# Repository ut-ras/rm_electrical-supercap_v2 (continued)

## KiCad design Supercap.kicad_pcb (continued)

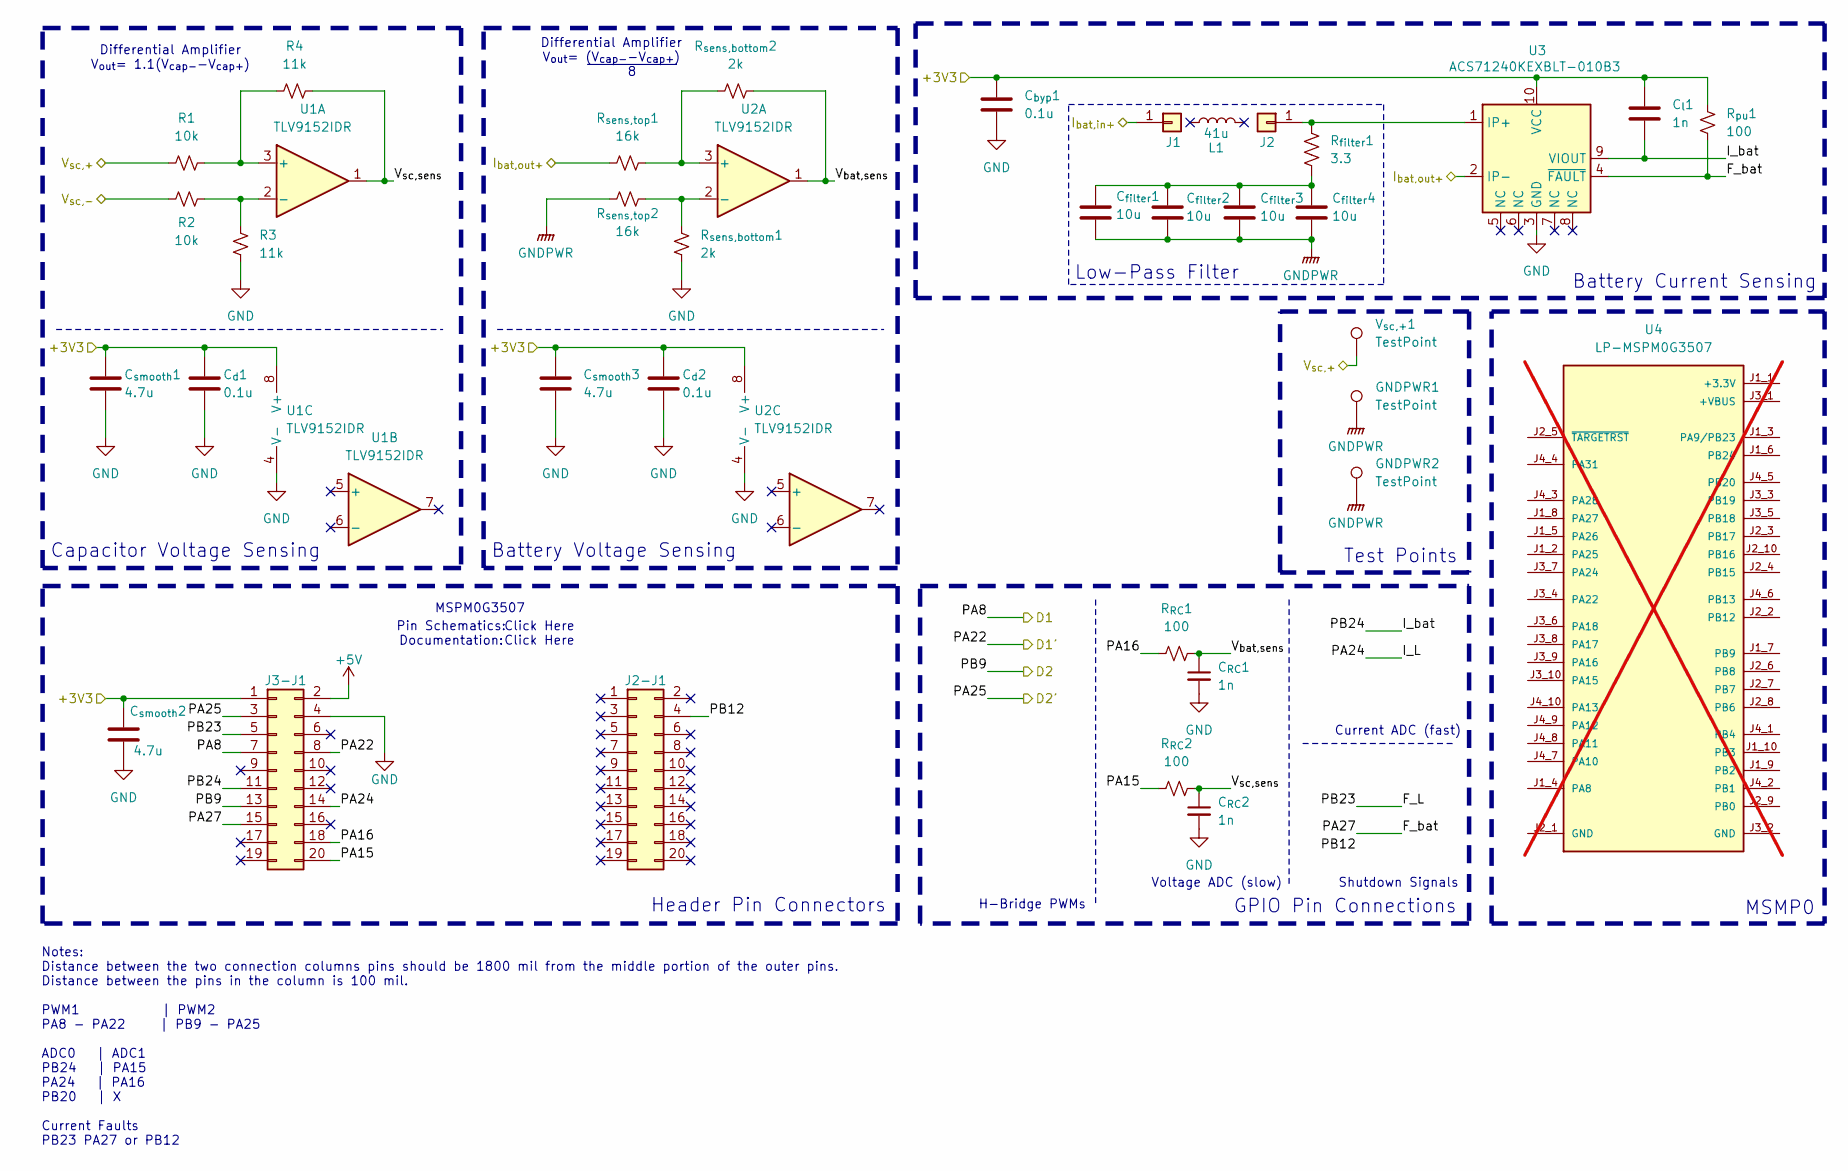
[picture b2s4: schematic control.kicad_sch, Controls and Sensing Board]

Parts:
C_{RC}1, C_{RC}2: 1n; C_0603_1608Metric_Pad1.08x0.95mm_HandSolder; Manufacturer_Part_Number CC0603JRX7R7BB102; Mouser Part Number 603-CC0603JR7R7BB102
C_{byp}1: 0.1u; C_0603_1608Metric_Pad1.08x0.95mm_HandSolder; Manufacturer_Part_Number MCAST168SB5104KTNA01; Mouser Part Number 963-MCAST168SB5104KT
C_{d}1, C_{d}2: 0.1u; C_0603_1608Metric_Pad1.08x0.95mm_HandSolder; Manufacturer_Part_Number KGM15BR71H104JM; Mouser Part Number 581-KGM15BR71H104JM
C_{filter}1, C_{filter}2, C_{filter}3, C_{filter}4: 10u; C_0603_1608Metric_Pad1.08x0.95mm_HandSolder; Mouser# 81-GRM188R6YA106MA3D
C_{l}1: 1n; C_0603_1608Metric_Pad1.08x0.95mm_HandSolder; Manufacturer_Part_Number CC0603JRX7R7BB102; Mouser Part Number 603-CC0603JR7R7BB102
C_{smooth}1, C_{smooth}2, C_{smooth}3: 4.7u; C_0603_1608Metric_Pad1.08x0.95mm_HandSolder; Manufacturer_Part_Number CL10A475KO8NNNC; Mouser Part Number 187-CL10A475KO8NNNC
GNDPWR1, GNDPWR2: TestPoint; TestPoint_Bridge_Pitch2.0mm_Drill0.7mm
J1, J2: Conn_01x01; Inductor_wire_conn
J2-J1, J3-J1: Conn_01x10; PinSocket_2x10_P2.54mm_Vertical; Manufacturer_Part_Number 2044-2X10G00SA; Digi-Key Part Number 2553-2044-2X10G00SA-ND
L1: 41u
R1, R2: 10k; R_0603_1608Metric_Pad0.98x0.95mm_HandSolder; Manufacturer_Part_Number RN73R1JTTD1002B50; Mouser Part Number 660-RN73R1JTD1002B50
R3, R4: 11k; R_0603_1608Metric_Pad0.98x0.95mm_HandSolder; Manufacturer_Part_Number RN73R1JTTD1102B25; Mouser Part Number 660-RN73R1JTD1102B25
R_{RC}1, R_{RC}2: 100; R_0603_1608Metric_Pad0.98x0.95mm_HandSolder; Manufacturer_Part_Number CRGCQ0603F100R; Mouser Part Number 279-CRGCQ0603F100R
R_{filter}1: 3.3; R_0603_1608Metric_Pad0.98x0.95mm_HandSolder; Manufacturer_Part_Number ERJ-H3QD3R30V; Mouser Part Number 667-ERJ-H3QD3R30V
R_{pu}1: 100; R_0603_1608Metric_Pad0.98x0.95mm_HandSolder; Manufacturer_Part_Number CRGCQ0603F100R; Mouser Part Number 279-CRGCQ0603F100R
R_{sens,bottom}1, R_{sens,bottom}2: 2k; R_0603_1608Metric_Pad0.98x0.95mm_HandSolder; Manufacturer_Part_Number AT0603DRD072KL; Mouser Part Number 603-AT0603DRD072KL
R_{sens,top}1, R_{sens,top}2: 16k; R_0603_1608Metric_Pad0.98x0.95mm_HandSolder; Manufacturer_Part_Number RT0603DRD0716KL; Mouser Part Number 603-RT0603DRD0716KL
U1, U2: TLV9152IDR; SOIC-8_3.9x4.9mm_P1.27mm; Manufacturer_Part_Number TLV9152IDR; Mouser Part Number 595-TLV9152IDR
U3: ACS71240KEXBLT-010B3; Allegro_QFN-12-10-1EP_3x3mm_P0.5mm; Manufacturer_Part_Number ACS71240KEXBLT-010B3; Mouser Part Number 250-71240KEXBLT010B3
U4: LP-MSPM0G3507; ti_LP_MSPM0G3507; not fitted
V_{sc,+}1: TestPoint; TestPoint_Bridge_Pitch2.0mm_Drill0.7mm

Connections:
+5V: J3-J1.2
/Control/+3V3: C_{byp}1.1, C_{d}1.1, C_{d}2.1, C_{l}1.1, C_{smooth}1.1, C_{smooth}2.1, C_{smooth}3.1, J3-J1.1, R_{pu}1.2, U1.8 (V+), U2.8 (V+), U3.10 (VCC); also elsewhere on the board
/Control/F_L: J3-J1.5
/Control/F_bat: J3-J1.15, R_{pu}1.1, U3.4 (~FAULT)
/Control/I_L: J3-J1.14
/Control/I_bat: C_{l}1.2, J3-J1.11, U3.9 (VIOUT)
/Control/I_{bat,in+}: J1.1; also elsewhere on the board
/Control/I_{bat,out+}: R_{sens,top}1.1, U3.2 (IP-); also elsewhere on the board
/Control/PA8: J3-J1.7; also elsewhere on the board
/Control/PA15: J3-J1.20, R_{RC}2.2
/Control/PA16: J3-J1.18, R_{RC}1.2
/Control/PA22: J3-J1.8; also elsewhere on the board
/Control/PA25: J3-J1.3; also elsewhere on the board
/Control/PB9: J3-J1.13; also elsewhere on the board
/Control/PB12: J2-J1.4
/Control/V_{bat,sens}: C_{RC}1.1, R_{RC}1.1, R_{sens,bottom}2.2, U2.1
/Control/V_{sc,+}: R1.1, V_{sc,+}1.1; also elsewhere on the board
/Control/V_{sc,sens}: C_{RC}2.1, R4.2, R_{RC}2.1, U1.1
/Voltage Converter/V_{sw,2}: R2.1; also elsewhere on the board
GND: C_{RC}1.2, C_{RC}2.2, C_{byp}1.2, C_{d}1.2, C_{d}2.2, C_{smooth}1.2, C_{smooth}2.2, C_{smooth}3.2, J3-J1.4, R3.2, R_{sens,bottom}1.1, U1.4 (V-), U2.4 (V-), U3.3 (GND); also elsewhere on the board
GNDPWR: C_{filter}1.2, C_{filter}2.2, C_{filter}3.2, C_{filter}4.2, GNDPWR1.1, GNDPWR2.1, R_{sens,top}2.1; also elsewhere on the board
unnamed: C_{filter}1.1, C_{filter}2.1, C_{filter}3.1, C_{filter}4.1, R_{filter}1.2
unnamed: J2.1, R_{filter}1.1, U3.1 (IP+)
unnamed: R1.2, R4.1, U1.3 (+)
unnamed: R2.2, R3.1, U1.2 (-)
unnamed: R_{sens,bottom}2.1, R_{sens,top}1.2, U2.3 (+)
unnamed: R_{sens,bottom}1.2, R_{sens,top}2.2, U2.2 (-)

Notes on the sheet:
Shutdown Signals
Pin Schematics: Documentation:
MSMP0
MSPM0G3507
Battery Current Sensing
Current ADC (fast)
Low-Pass Filter
Voltage ADC (slow)
Header Pin Connectors
Click Here
Differential Amplifier V_{out}= (V_{cap-}-V_{cap+}) ~{ 8 }
Test Points
GPIO Pin Connections
H-Bridge PWMs
Capacitor Voltage Sensing
Battery Voltage Sensing
Differential Amplifier V_{out}= 1.1(V_{cap-}-V_{cap+})
Notes: Distance between the two connection columns pins should be 1800 mil from the middle portion of the outer pins. Distance between the pins in the column is 100 mil. PWM1 | PWM2 PA8 - PA22 | PB9 - PA25 ADC0 | ADC1 PB24 | PA15 PA24 | PA16 PB20 | X Current Faults PB23 PA27 or PB12

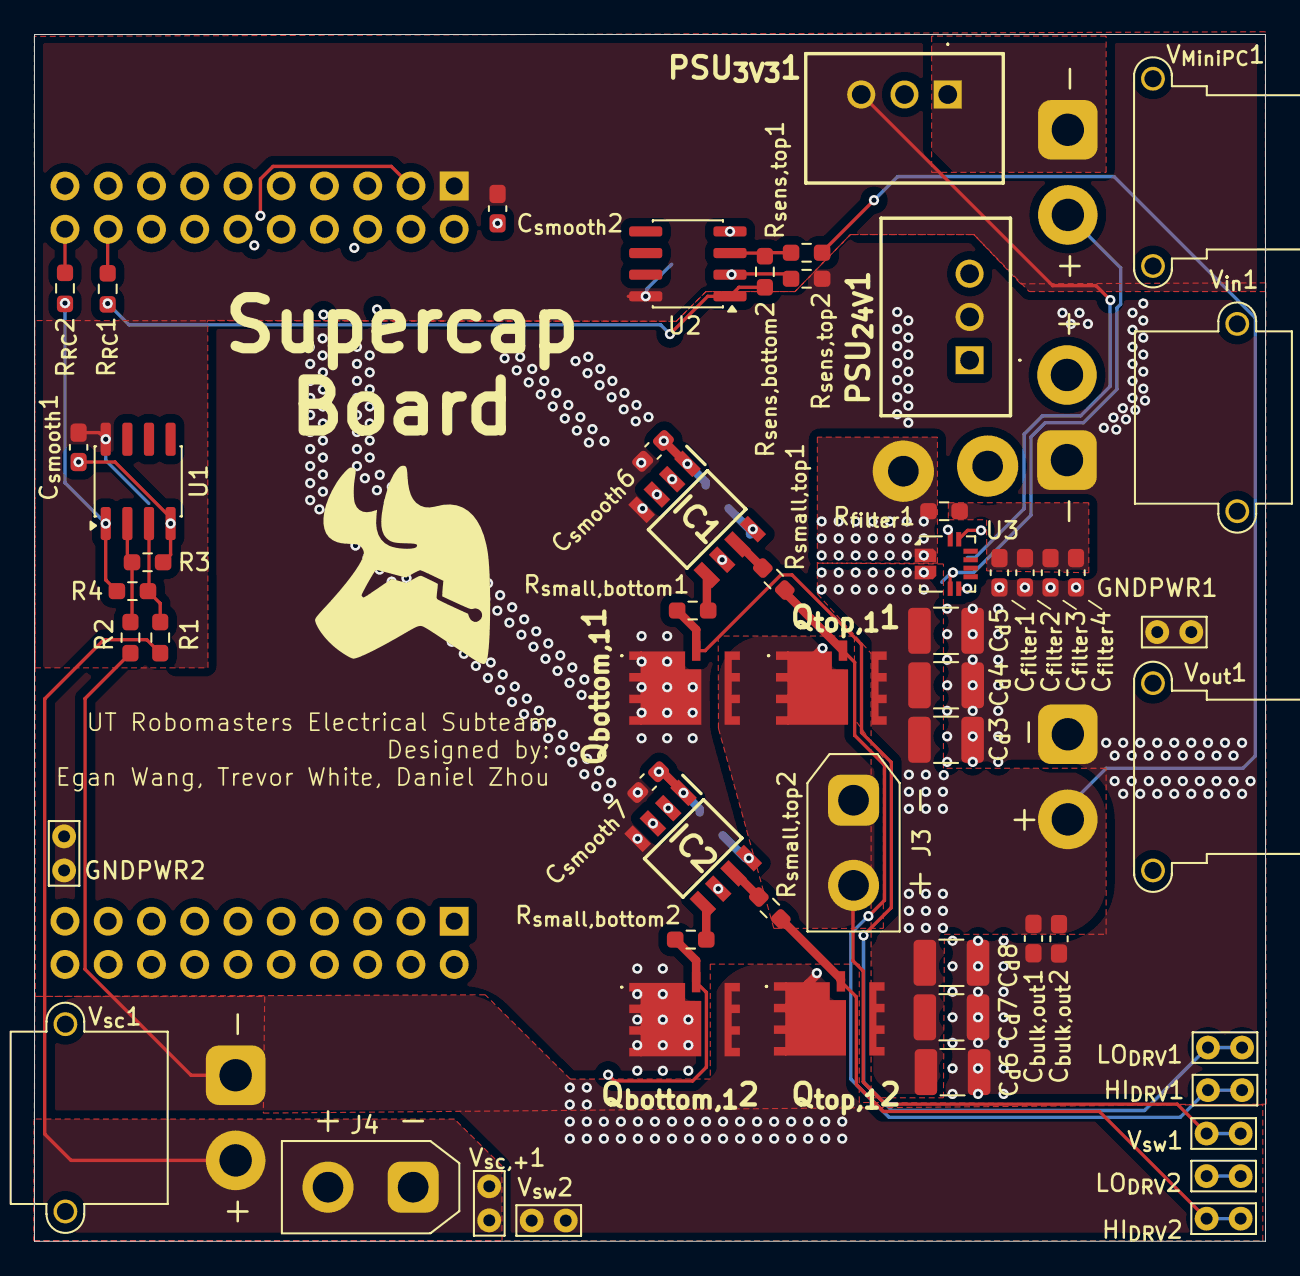
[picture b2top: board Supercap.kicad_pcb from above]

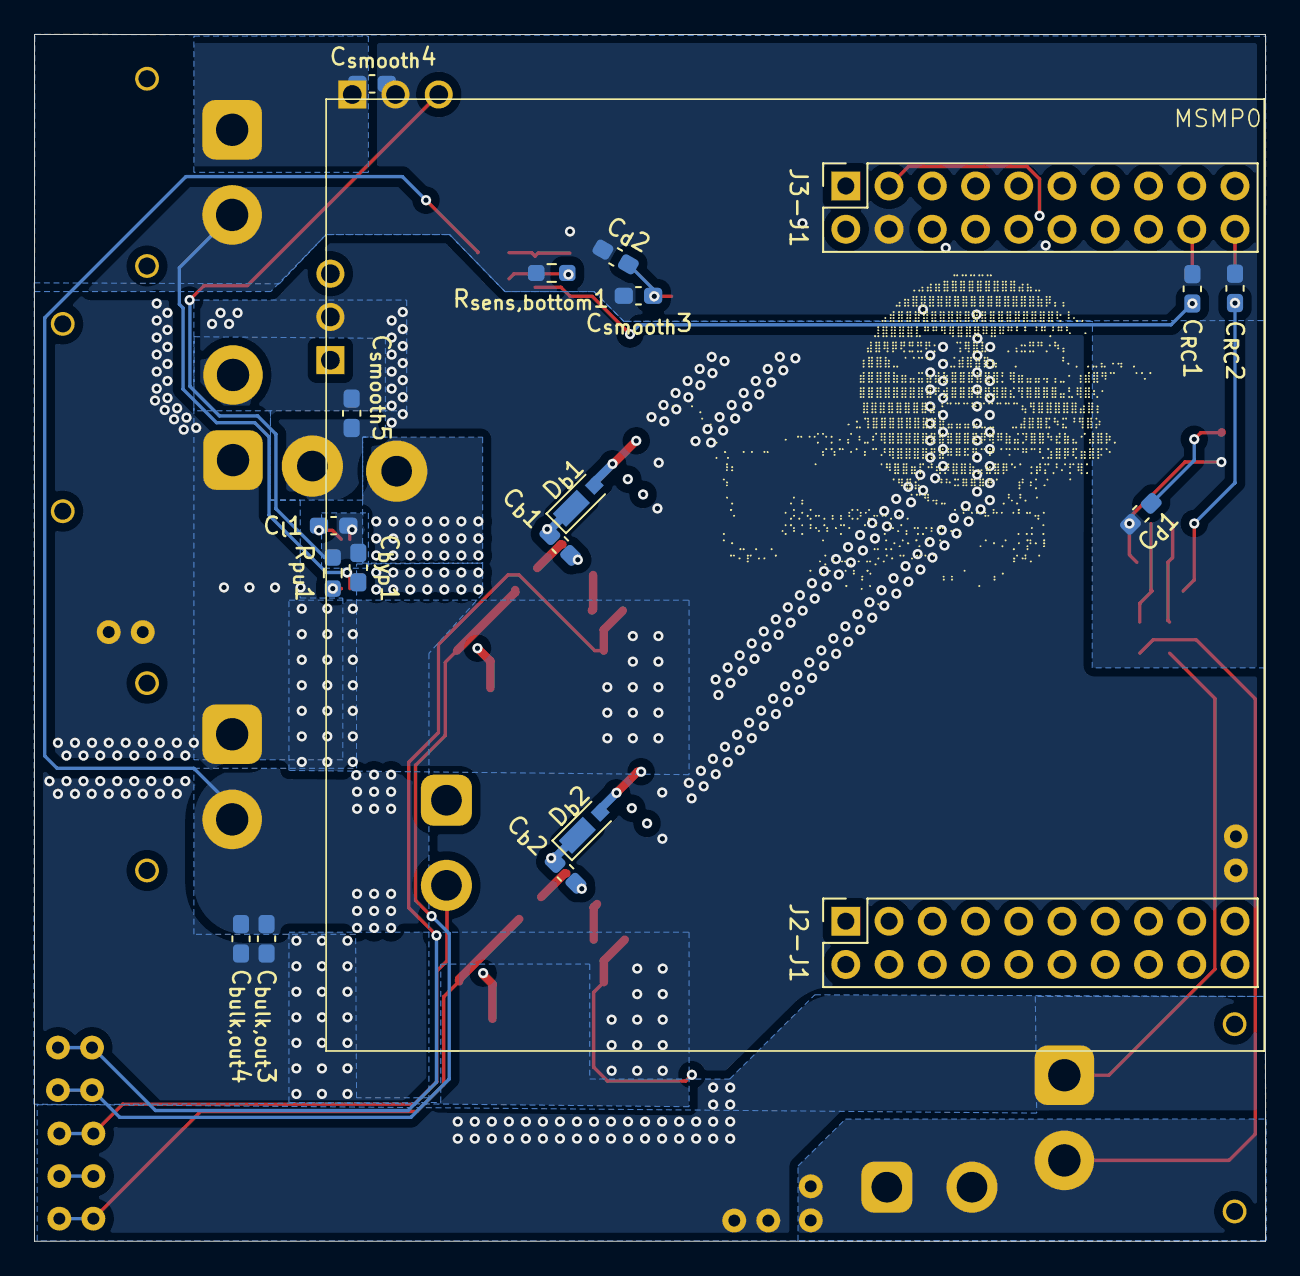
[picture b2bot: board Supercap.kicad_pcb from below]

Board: 4 copper layers, 72.3 x 70.9 mm, 77 parts (20 on the bottom side), 36 nets.

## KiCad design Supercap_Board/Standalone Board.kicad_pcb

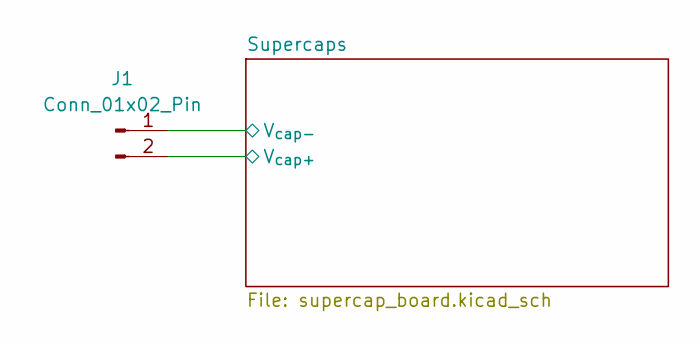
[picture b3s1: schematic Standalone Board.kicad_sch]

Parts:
J1: Conn_01x02_Pin; AMASS_XT30UPB-F_1x02_P5.0mm_Vertical

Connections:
/Supercaps/V_{cap+}: J1.2; also elsewhere on the board
/Supercaps/V_{cap-}: J1.1; also elsewhere on the board

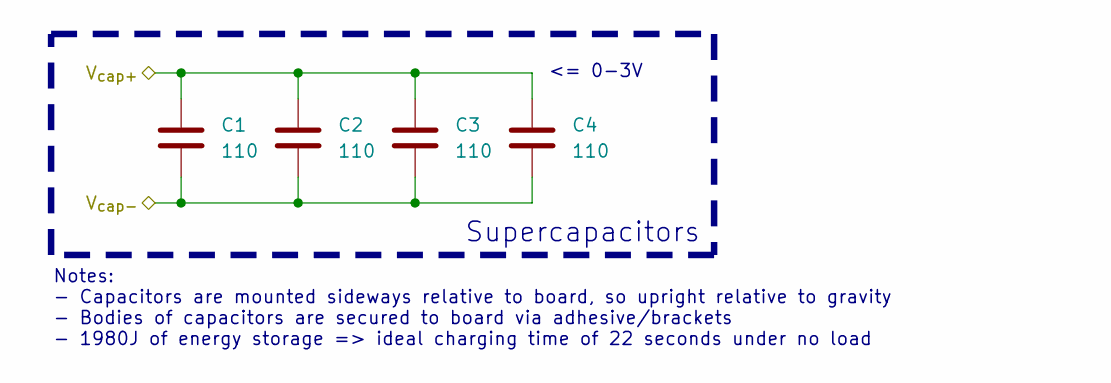
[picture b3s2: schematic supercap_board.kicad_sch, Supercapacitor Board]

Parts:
C1, C2, C3, C4: 110; C_Radial_D18.0mm_H35.5mm_P7.50mm; Voltage Rating 3V; Mouser Part Number 598-DSF117Q3R0

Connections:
/Supercaps/V_{cap+}: C1.1, C2.1, C3.1, C4.1; also elsewhere on the board
/Supercaps/V_{cap-}: C1.2, C2.2, C3.2, C4.2; also elsewhere on the board

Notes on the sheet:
Notes: - Capacitors are mounted sideways relative to board, so upright relative to gravity - Bodies of capacitors are secured to board via adhesive/brackets - 1980J of energy storage => ideal charging time of 22 seconds under no load
Supercapacitors
<= 0-3V

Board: 2 copper layers, 5 parts (0 on the bottom side), 2 nets, no tracks yet.

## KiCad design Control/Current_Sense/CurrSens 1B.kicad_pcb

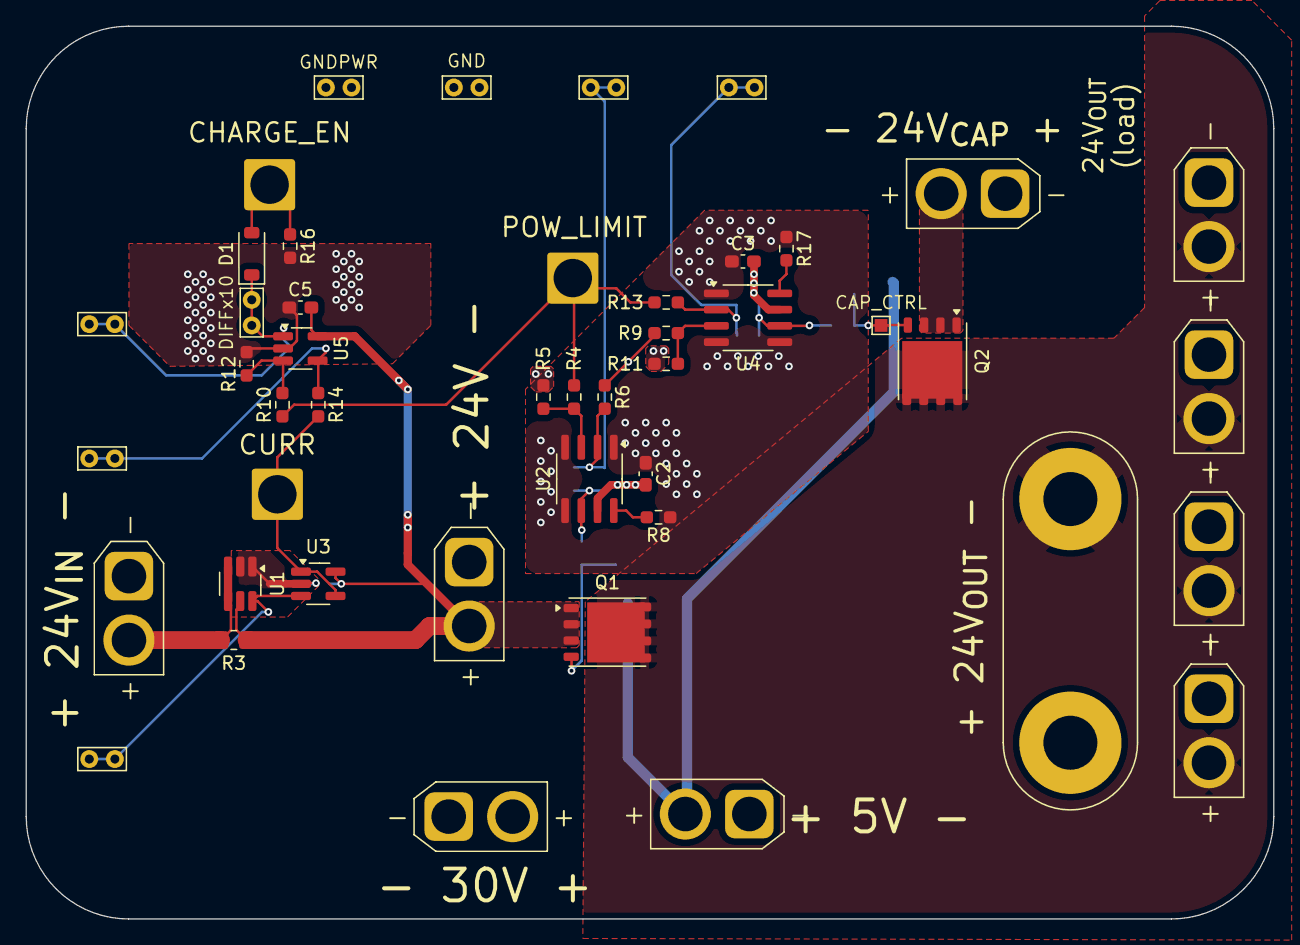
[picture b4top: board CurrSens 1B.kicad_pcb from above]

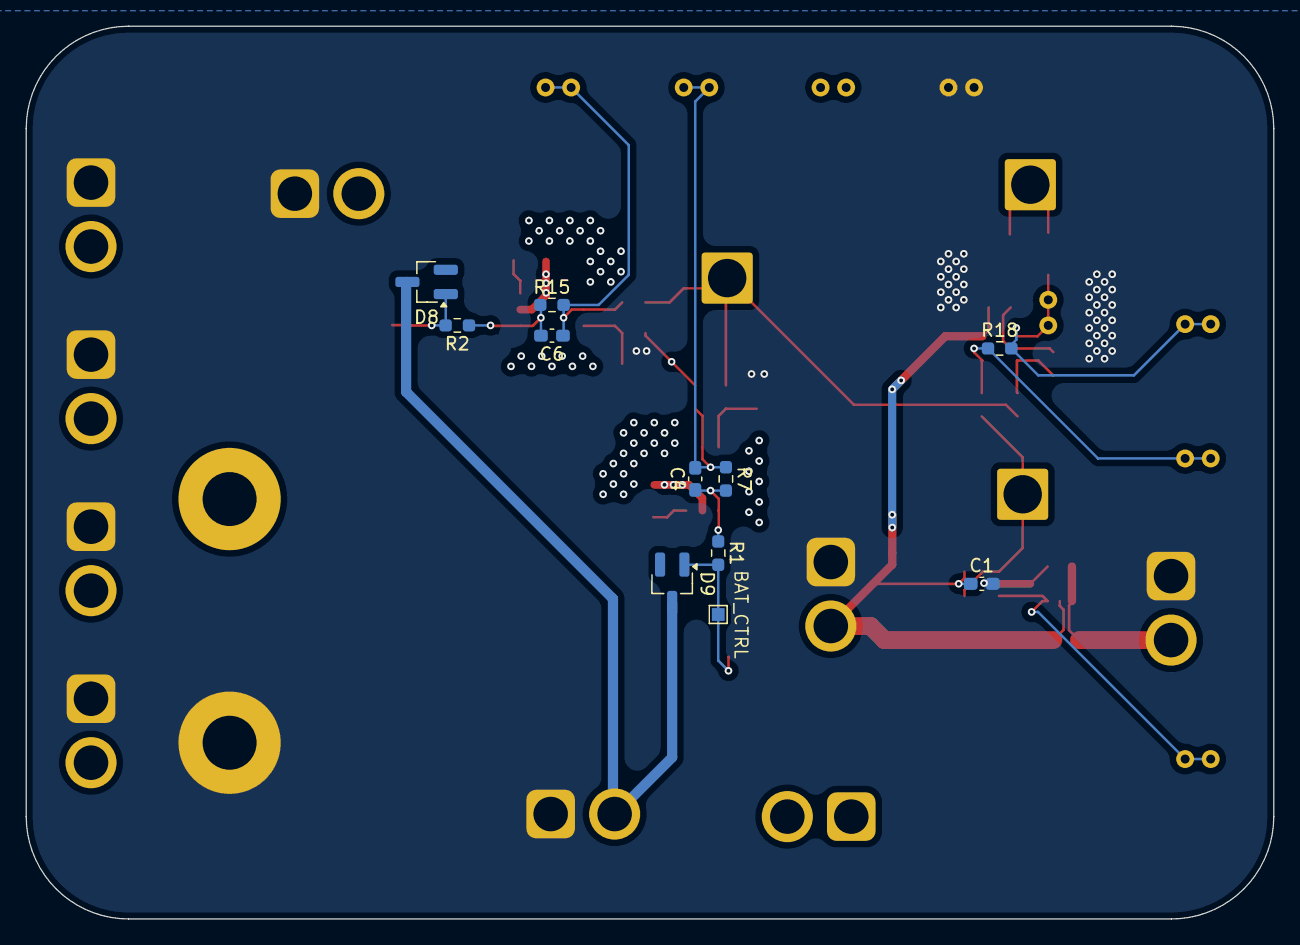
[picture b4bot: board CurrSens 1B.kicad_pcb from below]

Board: 4 copper layers, 97.5 x 69.8 mm, 57 parts (11 on the bottom side), 25 nets.

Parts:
C1, C2, C3, C5: 0.1u; C_0603_1608Metric_Pad1.08x0.95mm_HandSolder
C4, C6: 1000p; C_0603_1608Metric_Pad1.08x0.95mm_HandSolder
D1: MMSZ4678T1G; D_SOD-123
D8, D9: BAT54; SOT-23_Handsoldering
J1, J2, J10: Conn_01x01_Pin; SolderWire-2.5sqmm_1x01_D2.4mm_OD3.6mm
J3, J6, J7, J9, J11, J12, J13, J14, J15: XT30_F; AMASS_XT30U-F_1x02_P5.0mm_Vertical
J16: Banana; RM_Banana_Jack_2Pin
Q1, Q2: BSC059N04LS6; Infineon_PG-TDSON-8_6.15x5.15mm
R1, R2: 0; R_0603_1608Metric_Pad0.98x0.95mm_HandSolder
R3: 0.02; R_0805_2012Metric_Pad1.20x1.40mm_HandSolder
R4, R6, R9, R13: 1k; R_0603_1608Metric_Pad0.98x0.95mm_HandSolder
R5, R7, R11, R12, R15, R18: 1Meg; R_0603_1608Metric_Pad0.98x0.95mm_HandSolder
R8, R17: 47k; R_0603_1608Metric_Pad0.98x0.95mm_HandSolder
R10, R14: 100k; R_0603_1608Metric_Pad0.98x0.95mm_HandSolder
R16: 15k; R_0603_1608Metric_Pad0.98x0.95mm_HandSolder
TP1, TP2, TP3: V_{DIFF10}; TestPoint_Bridge_Pitch2.0mm_Drill0.7mm
TP4, TP5: V_{DIFF10}; TestPoint_Pad_1.0x1.0mm
TP6: CE_OUT; TestPoint_Bridge_Pitch2.0mm_Drill0.7mm
TP7: CE_IN_NEG; TestPoint_Bridge_Pitch2.0mm_Drill0.7mm
TP8: I_OUT; TestPoint_Bridge_Pitch2.0mm_Drill0.7mm
TP9: CAP_IN_NEG; TestPoint_Bridge_Pitch2.0mm_Drill0.7mm
TP10: BAT_IN_NEG; TestPoint_Bridge_Pitch2.0mm_Drill0.7mm
U1: MAX4073T; SOT-23-6_Handsoldering
U2, U4: OPA551U; SOIC-8_3.9x4.9mm_P1.27mm
U3, U5: TLV9301xDBV; SOT-23-5_HandSoldering

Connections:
+5V: D8.3 (A), D9.3 (A), J12.2
+24V: C1.1, C5.1, J13.2, Q1.1 (S), Q1.2 (S), Q1.3 (S), R3.2, U1.5 (RS-), U3.5 (V+), U5.5 (V+)
/+24V_CAP_IN: J14.2, Q2.1 (S), Q2.2 (S), Q2.3 (S)
/+24_IN: J15.2, R3.1, U1.3 (Vcc), U1.4 (RS+)
/+24_MERGED: J3.2, J6.2, J7.2, J9.2, J16.2, Q1.5 (D), Q2.5 (D)
/BAT_CTRL: C4.2, R1.1, R7.2, U2.6
/BAT_CTRL_R: D9.1 (K), Q1.4 (G), R1.2, TP5.1
/CAP_CTRL: C6.2, R2.1, R15.2, U4.6
/CAP_CTRL_R: D8.1 (K), Q2.4 (G), R2.2, TP4.1
/CHARGE_EN_OUT: D1.2 (A), J10.1, R16.2
/CURR_OUT: J2.1, R6.1, R9.1, R14.1, U3.1, U3.4 (-)
/Current Sense/1+: R4.2, R5.2, U2.3 (+)
/Current Sense/1-: C4.1, R6.2, R7.1, TP10.1, U2.2 (-)
/Current Sense/2+: R9.2, R11.2, U4.3 (+)
/Current Sense/2-: C6.1, R13.2, R15.1, TP9.1, U4.2 (-)
/Current Sense/3+: R10.2, R12.2, U5.3 (+)
/Current Sense/3-: R14.2, R18.1, TP7.1, U5.4 (-)
/Current Sense/CURR_{RAW}: TP8.1, U1.6 (OUT), U3.3 (+)
/Current Sense/DIFF10: D1.1 (K), R18.2, TP1.1, TP6.1, U5.1
/Current Sense/FLAG_{1}: R8.1, U2.8 (Flag)
/Current Sense/FLAG_{2}: R17.1, U4.8 (Flag)
/POW_LIMIT_IN: J1.1, R4.1, R10.1, R13.1
GND: C2.2, C3.2, J11.1, R8.2, R17.2, TP2.1, U2.1 (V-), U2.4 (V-), U2.5 (V-), U4.1 (V-), U4.4 (V-), U4.5 (V-)
GNDPWR: C1.2, C5.2, J3.1, J6.1, J7.1, J9.1, J12.1, J13.1, J14.1, J15.1, J16.1, R5.1, R11.1, R12.1, R16.1, TP3.1, U1.1 (GND), U1.2 (GND), U3.2 (V-), U5.2 (V-)
VCC: C2.1, C3.1, J11.2, U2.7 (V+), U4.7 (V+)

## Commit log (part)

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2025-10-31 Initial organization and commit
2025-10-31 New directories for subcircuits/designs
2025-10-31 add input buck
2025-11-01 Current Sense
2025-11-02 began setup of hierarchial boards for supercap
2025-11-04 added more flesh to overall structure, primarily on converter stage
2025-11-05 finished first pass of general block diagram
2025-11-05 replaced 2p2s caps with full parallel
2025-11-09 created PLECS simulation file, need to figure out what is going on with ringing behavior
2025-11-15 Updated power stage PLECS simulation
2025-11-22 added switch-cycle average model with parameters for constant current control in open loop
2025-11-27 removed unnecessary critical loop
2025-12-20 switched capacitor topology to 4S
2026-01-30 changed converter topology to full-bridge design
2026-02-08 dc/dc converter
2026-02-10 added presentation for professors, updated PLECS models
2026-02-15 began work on adding gate driver circuitry
2026-02-16 Added schematic, footprints, and datasheets for voltage sense
2026-02-20 added symbol libraries and finished gate driver circuitry schematic
2026-02-22 fixed converter section
2026-02-22 housekeeping_2
2026-02-22 MSPM0 Connections
2026-02-22 added mosfet footprints and assigned to switch symbols
2026-02-22 Diff Amp
2026-02-22 housekeeping-added-2
2026-02-22 updated PLECs simulations
2026-02-22 assigned footprints for some passives
2026-02-26 added inductor design file
2026-03-01 12Vmodified
2026-03-01 attempting to push kicad library mosfet sym/foot
2026-03-01 more simulation work + fixed some things in root schematic
2026-03-01 DCDCconverter modified
2026-03-01 wiring connected, now only need msmp0 pinout and footprint assignments
2026-03-01 fixed inductor connection
2026-03-01 decoupling capacitors assigned
2026-03-01 removed v1 files and assigned mouser part numbers
2026-03-02 began layout
2026-03-03 mostly done with first order layout
2026-03-04 I FINALLY FIGURED OUT THE CONTROL SCHEME I NEEDED A SQUARE ROOT
2026-03-06 more changes to sims for reverse engineering
2026-03-06 added sample data to MATLAB
2026-03-06 fixed merge conflict in average mode
2026-03-06 Added program to fit exponential decay function to data points
2026-03-07 critical loops trace
2026-03-08 more controls work
2026-03-08 hopefully: did crit and driver loops for rt half bridge, swapped decoupling caps and Cd/Csmooth 6 and 7 for organization purposes
2026-03-08 bigger trace push before trevor starts
2026-03-08 added linearized model
2026-03-08 Fits curve to two data sets for ease of comparison
2026-03-08 ok hopefully this doesnt break everything, committing after doing in kicadlib submod
2026-03-08 FirmWare
2026-03-08 added mspm0 fp, still need to map pin nets on sym in schematic, in process of doing redesign to min power path
2026-03-09 WORKING SWITCH-CYCLE AVERAGE MODEL LESGOOOOOO
2026-03-10 more screwing around with open loop control
2026-03-11 added toy model
2026-03-11 Created quadratic linearization model
2026-03-11 started work on slides explaining linearization
2026-03-12 updated toy model
2026-03-12 fixing inprogress files from previous commit
2026-03-12 finished PI+FF presentation
2026-03-12 large expansion to explanation powerpoint + some brushing up on toy model
2026-03-12 evil and intimidating file embed
2026-03-12 more slides
2026-03-12 I really need to remember to close PLECS before committing
2026-03-12 identified new issue
2026-03-13 via stitching on fets, fixed sheet pin (not label on parent) for isense, messed around with design
2026-03-14 still trying to get discharging cycle to work
2026-03-21 big progress on layout
2026-03-21 FINISHED EXCEPT FOR FAULT TRACES YIPPEE
2026-03-22 jed irl review
2026-03-23 Fault Code & Pins
    Added the config for the hardware fault handing of the current sensors. When the fault signal falls low all pwm signals and their complements are set to grounod. Additionally the traces for this were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
    Other: Changed some ADC input pins to avoid double use with the launch pad board.
2026-03-24 minor PCB tweaks
2026-03-24 made corners better for switch nodes, hopefully
2026-03-27 cleaned up sections to be repositioned
2026-03-27 started work on reverse charging functionality
2026-03-27 need to see other board
2026-03-28 need to pu v1 to make copy on other desktop
2026-03-28 im so bad at this :skull Vsc+ pour boutta go crazy, the mspm0 pin buses too, idk if i even got what i did right lmao but ill figure it out later
2026-03-28 updated powerpoint
2026-03-29 finished sensitivity theoretical section of powerpoint
2026-03-29 still can't figure out algebraic loop error
2026-03-29 Trevor2.0
2026-03-29 Closed loop transfer function sensitivities
2026-03-29 Sensitivities
2026-03-29 getting paranoid that kicads gonna crash: moved current sense IC and inductor pad assoc. drew rest of main pours for cap charging, gndpwr, etc
2026-03-29 sensitvity errors
2026-03-29 Added Noise
2026-03-29 transfer function moving
2026-03-29 Added sensitivity to last slide
2026-03-29 updated sensitivity
2026-03-29 finished moving files
2026-03-29 finished foundation pours, layout, tp routing along edges. Next: cursed routing I sense IC/H to 3v3, 3v3 to mspm0
2026-03-29 Sensor White Noise Slide
2026-03-30 sync
2026-03-30 removed PI2 control and improved disturbance rejection from PI
2026-04-01 FAULT HANDELR WORKING!!!!
    There is still an issue where the ISR is not running so we currently can't clear the fault but that might be desired.
2026-04-01 inductor design file
2026-04-02 updated PLECs model to use new inductor parameters
2026-04-05 that took a lot longer than i thought and so cursed. looks kinda cool though, finished the H bridge/3v3/mspm0 traces, tried to keep along edges. holding off on via stitching just yet cuz im sure glor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
2026-04-05 small things, trevor checked, awaiting heavenly mandated egan
2026-04-05 glitching out, some stitching
2026-04-05 worked a lil on the FFPI
    Problem with imported math function but the code is saved in a text document called FFPI
2026-04-05 Should I go to my Ex's Choir Concert?
2026-04-05 Trevor is a genius, flipped mspm0 pins, in progress: 3v3 rerouting/redesign, edge pathing, deleting old stuff, etc.
2026-04-10 Matlab for LC filter
2026-04-10 put filters closer to IC's, cleared up some stuff, still gonna have cool cross board bus prob yipee
2026-04-11 Matlab and Excel for Pi filter values, poles, and zero
2026-04-11 matlab
2026-04-11 moved file
2026-04-11 moving files
2026-04-12 done, routed everything, todo: DRC
2026-04-12 updated matlab + Bode plotting
2026-04-12 DRC, cleared up all errors except 2 that are unavoidable with board settings (2 pads on the same ic being too close). Warnings are vast majority of the silkscreen, solder mask type. A few important w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
2026-04-12 small
2026-04-12 starting on V3 :) yipee. finished pours and stuff
2026-04-13 laid out PCB rev C
2026-04-14 finished prelim board layout pending filter inductor redesign
2026-04-14 added parallel capacitance, minor cleanup to design - jed review + approval
2026-04-14 added heatsinks + more bulk capacitance footprints
2026-04-14 added better smoothing behavior to power supplies and op-amps as per application notes, switched resistors to op-amp with higher values
2026-04-14 minor tweaks to model + filter design
2026-04-15 split into separate boards as per regulations
2026-04-15 added more diagnostics for the PI loop
2026-04-15 still need to finish housekeeping power supply footprints
2026-04-15 cleaned up PCB after meeting with BBJ
2026-04-15 created drill files
2026-04-15 BOM stuff
2026-04-16 made some progress on model blowing up
2026-04-16 plotted standalone board and updated KiCAD BOM (not spreadsheet BOM)
2026-04-17 new library updates
2026-04-17 Thx Tim
2026-04-17 added Heath revision
2026-04-21 going to run boost mode back
2026-04-21 beginning work on simulink
2026-04-26 added simulink simulation
2026-05-05 finished power stage modeling powerpoint
2026-05-07 big ahhhh merge + partial bringup guide written
2026-05-09 more bringup guide progress
